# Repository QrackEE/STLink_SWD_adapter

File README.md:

# ABOUT  This is simple adapter board to use STM SWD interface from STLink programmer. Mind that distance form external goldpin header row to programmer edge measures 8 mm for V2 version - check with your programmer before PCB run.# ReferenceConnections table is avaliable in [ST UM1075](https://www.st.com/content/ccc/resource/technical/document/user_manual/65/e0/44/72/9e/34/41/8d/DM00026748.pdf/files/DM00026748.pdf/jcr:content/translations/en.DM00026748.pdf) on page 12:

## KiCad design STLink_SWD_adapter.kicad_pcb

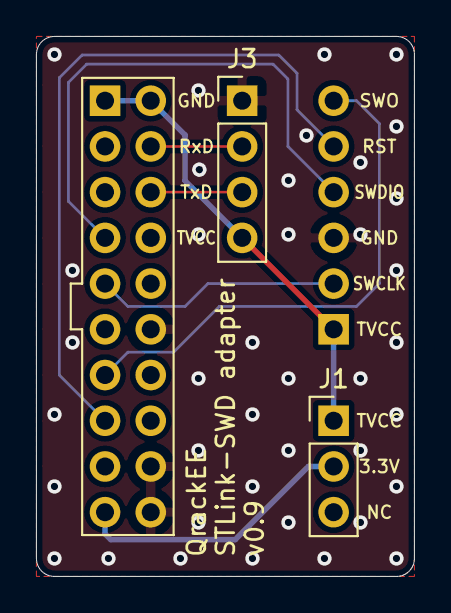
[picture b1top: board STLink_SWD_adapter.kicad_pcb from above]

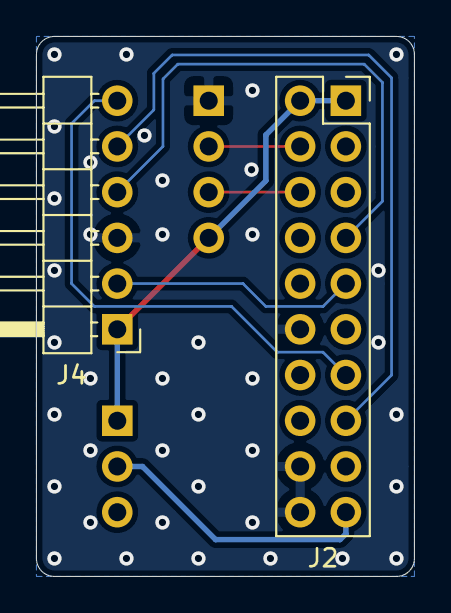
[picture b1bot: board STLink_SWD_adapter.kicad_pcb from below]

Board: 2 copper layers, 21.0 x 30.0 mm, 4 parts (2 on the bottom side), 9 nets.

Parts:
J1: Conn_01x03_Male; PinHeader_1x03_P2.54mm_Vertical
J2: Conn_02x10_Odd_Even; PinSocket_2x10_P2.54mm_Vertical
J3: Conn_01x04_Male; PinHeader_1x04_P2.54mm_Vertical
J4: Conn_01x06_Male; PinHeader_1x06_P2.54mm_Horizontal

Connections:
/STM32RESET: J2.15, J4.5
/TCK_SWCLK: J2.9, J4.2
/TDO_SWO: J2.13, J4.6
/TMS_SWDIO: J2.7, J4.4
/TVCC: J1.1, J2.1, J2.2, J3.4, J4.1
/UART_RX: J2.4, J3.2
/UART_TX: J2.6, J3.3
/VDD3.3V: J1.2, J2.19
GND: J2.12, J2.18, J2.20, J3.1, J4.3

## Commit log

2019-07-07 Initial design
2019-07-08 Because I like my corners round

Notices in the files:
STLink_SWD_adapter.kicad_pcb:
License: MIT
